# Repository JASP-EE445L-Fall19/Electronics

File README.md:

# Electronics
Schematics, Boards, and Libraries for Lab 11 project

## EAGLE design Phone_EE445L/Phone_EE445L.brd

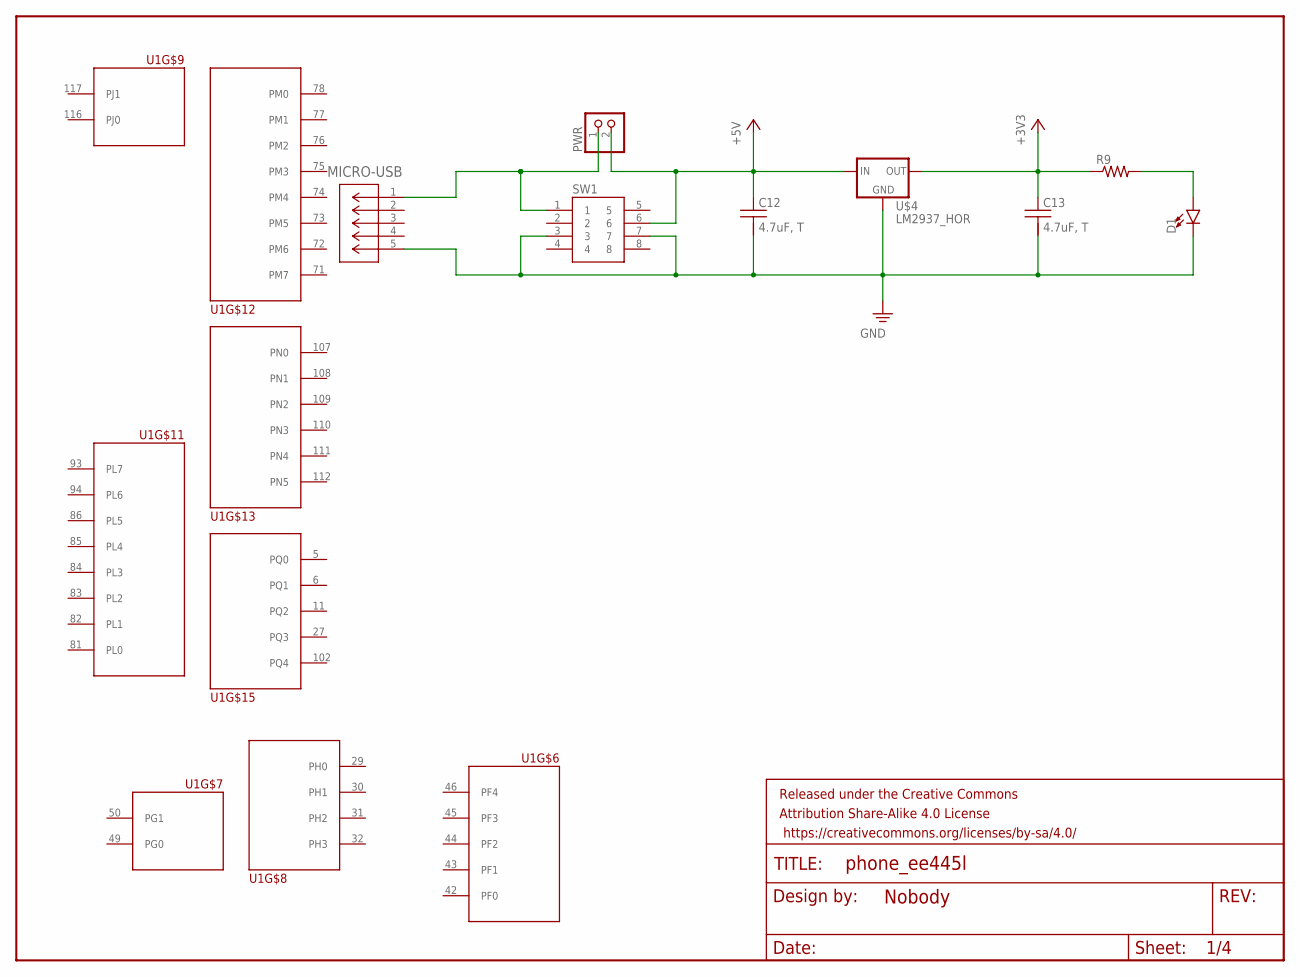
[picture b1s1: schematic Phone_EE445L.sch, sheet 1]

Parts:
C12, C13: 4.7uF, T; CAP200MIL
D1: LED0603; LED-0603
FRAME1: FRAME-LETTERNO_PACKAGE; DUMMY
MICRO-USB: ZX62D-B-5PA8(30); CONN5_ZX62D-B-5PA8
PWR: PINHD-1X2; 1X02
R9: R-US_R0805; R0805
SW1: PUSHBUTTON; PWRBUTTON
U1: TM4C129-MOD; TQFP-128
U$4: LM2937_HOR; TO220

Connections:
5VIN: MICRO-USB.1, PWR.1, SW1.1
+3V3: C13.1, R9.1, U$4.3 (OUT); also elsewhere on the board
+5V: C12.1, PWR.2, SW1.6, U$4.1 (IN); also elsewhere on the board
GND: C12.2, C13.2, D1.C, MICRO-USB.5, SW1.3, SW1.7, U$4.2 (GND); also elsewhere on the board
unnamed: D1.A, R9.2

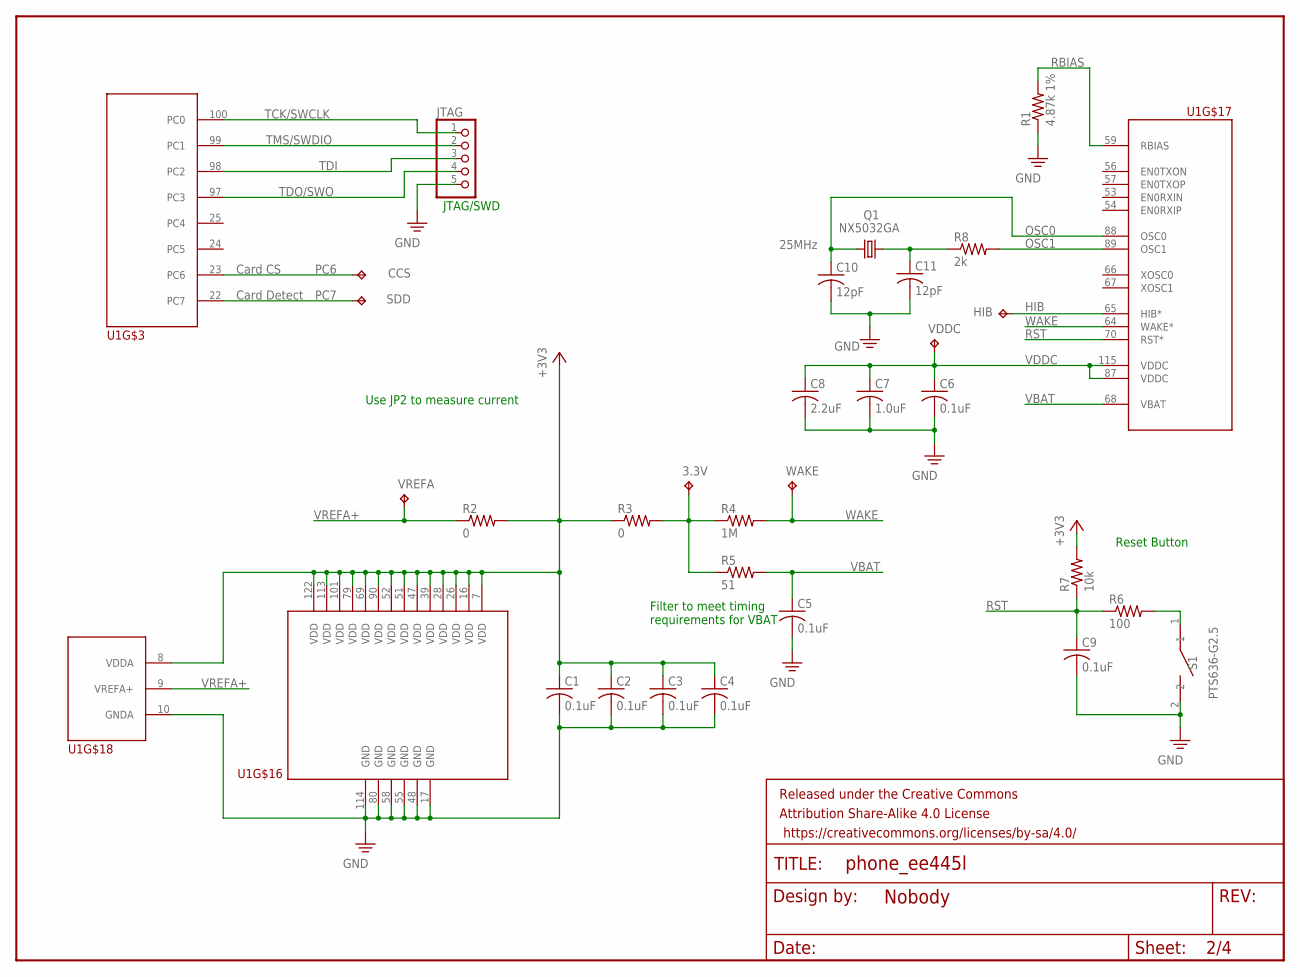
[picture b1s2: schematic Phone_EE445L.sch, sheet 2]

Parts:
3.3V: TP_KEYSTONE500X; P1.1MM
C1, C2, C3, C4, C5, C6, C9: 0.1uF; C0805
C7: 1.0uF; C0805
C8: 2.2uF; C0805
C10, C11: 12pF; C0805
CCS: TP_KEYSTONE500X; P1.1MM
FRAME2: FRAME-LETTERNO_PACKAGE; DUMMY
HIB: TP_KEYSTONE500X; P1.1MM
JTAG: PINHD-1X5; 1X05
Q1: NX5032GA
R1: 4.87k 1%; R0805
R2, R3: 0; R0805
R4: 1M; R0805
R5: 51; R0805
R6: 100; R0805
R7: 10k; R0805
R8: 2k; R0805
S1: PTS636-G2.5; PTS636-G
SDD: TP_KEYSTONE500X; P1.1MM
U1: TM4C129-MOD; TQFP-128
VDDC: TP_KEYSTONE500X; P1.1MM
VREFA: TP_KEYSTONE500X; P1.1MM
WAKE: TP_KEYSTONE500X; P1.1MM

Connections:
+3V3: C1.1, C2.1, C3.1, C4.1, R2.2, R3.1, R7.2, U1.7 (VDD), U1.8 (VDDA), U1.16 (VDD), U1.26 (VDD), U1.28 (VDD), U1.39 (VDD), U1.47 (VDD), U1.51 (VDD), U1.52 (VDD), U1.69 (VDD), U1.79 (VDD), U1.90 (VDD), U1.101 (VDD), U1.113 (VDD), U1.122 (VDD); also elsewhere on the board
GND: C1.2, C2.2, C3.2, C4.2, C5.2, C6.2, C7.2, C8.2, C9.2, C10.2, C11.2, JTAG.5, R1.1, S1.2, U1.10 (GNDA), U1.17 (GND), U1.48 (GND), U1.55 (GND), U1.58 (GND), U1.80 (GND), U1.114 (GND); also elsewhere on the board
HIB: HIB.TP, U1.65 (HIB*)
unnamed: C11.1, Q1.1, R8.1
unnamed: R6.2, S1.1
OSC0: C10.1, Q1.2, U1.88 (OSC0)
OSC1: R8.2, U1.89 (OSC1)
PC6: CCS.TP, U1.23 (PC6); also elsewhere on the board
PC7: SDD.TP, U1.22 (PC7); also elsewhere on the board
RBIAS: R1.2, U1.59 (RBIAS)
RST: C9.1, R6.1, R7.1, U1.70 (RST*)
TCK/SWCLK: JTAG.1, U1.100 (PC0)
TDI: JTAG.3, U1.98 (PC2)
TDO/SWO: JTAG.4, U1.97 (PC3)
TMS/SWDIO: JTAG.2, U1.99 (PC1)
VBAT: C5.1, R5.2, U1.68 (VBAT)
VDDC: C6.1, C7.1, C8.1, U1.87 (VDDC), U1.115 (VDDC), VDDC.TP
VREFA+: R2.1, U1.9 (VREFA+), VREFA.TP
WAKE: R4.2, U1.64 (WAKE*), WAKE.TP
WAKEVDD: 3.3V.TP, R3.2, R4.1, R5.1

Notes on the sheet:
JTAG/SWD
Filter to meet timing requirements for VBAT
Use JP2 to measure current
Reset Button
Card CS
Card Detect
25MHz

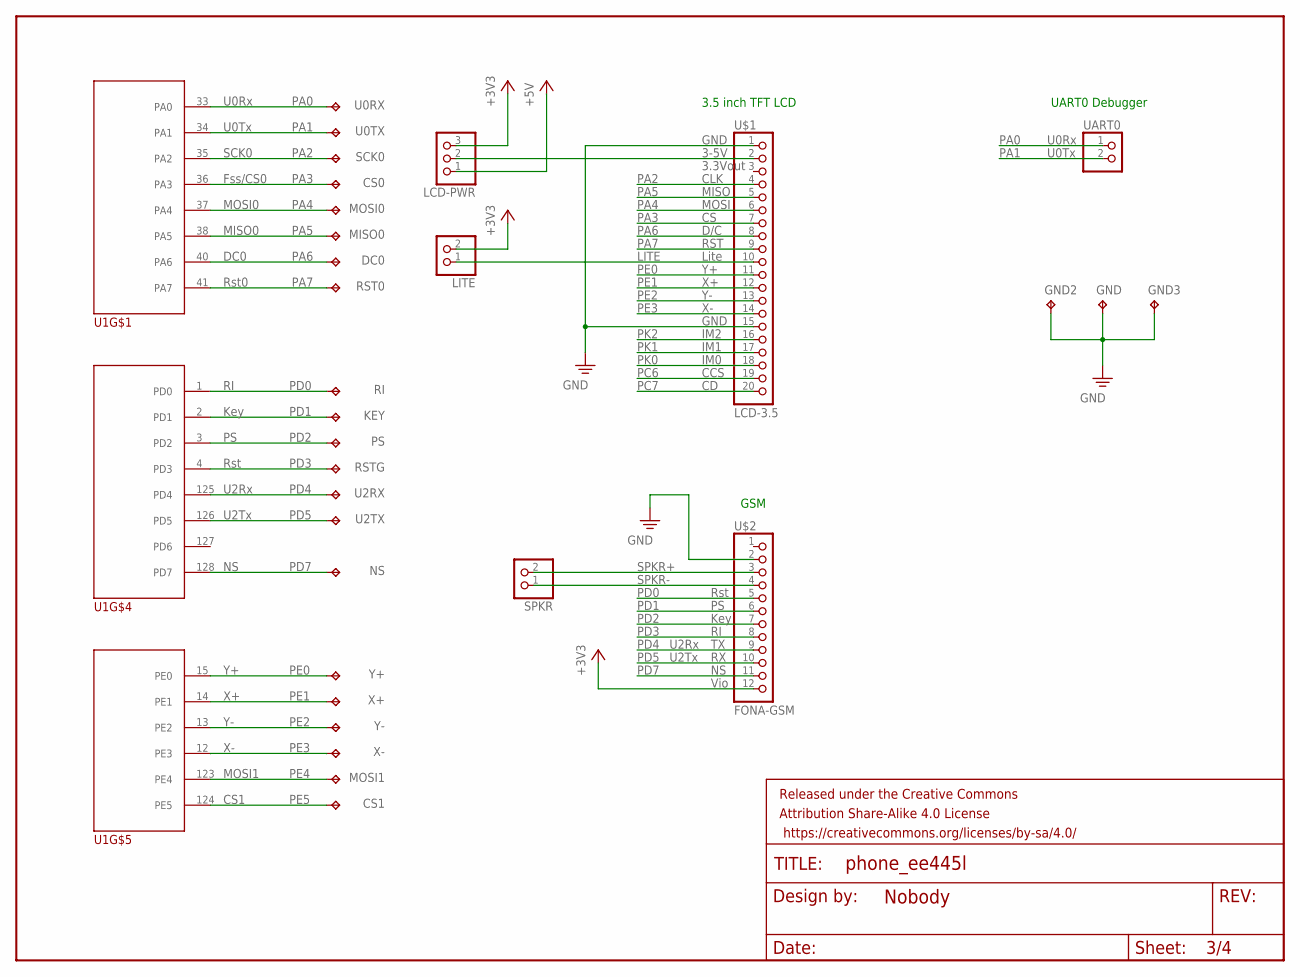
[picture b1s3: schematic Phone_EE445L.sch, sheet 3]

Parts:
CS0, CS1: TP_KEYSTONE500X; P1.1MM
DC0: TP_KEYSTONE500X; P1.1MM
FRAME3: FRAME-LETTERNO_PACKAGE; DUMMY
GND, GND2, GND3: TP_KEYSTONE500X; P1.1MM
KEY: TP_KEYSTONE500X; P1.1MM
LCD-PWR: PINHD-1X3; 1X03
LITE: PINHD-1X2; 1X02
MISO0: TP_KEYSTONE500X; P1.1MM
MOSI0, MOSI1: TP_KEYSTONE500X; P1.1MM
NS: TP_KEYSTONE500X; P1.1MM
PS: TP_KEYSTONE500X; P1.1MM
RI: TP_KEYSTONE500X; P1.1MM
RST0: TP_KEYSTONE500X; P1.1MM
RSTG: TP_KEYSTONE500X; P1.1MM
SCK0: TP_KEYSTONE500X; P1.1MM
SPKR: PINHD-1X2; 1X02
U0RX, U0TX, U2RX, U2TX: TP_KEYSTONE500X; P1.1MM
U1: TM4C129-MOD; TQFP-128
U$1: LCD-3.5; LCD3.5IN
U$2: FONA-GSM; FONA
UART0: PINHD-1X2; 1X02
X+: TP_KEYSTONE500X; P1.1MM
X-: TP_KEYSTONE500X; P1.1MM
Y+: TP_KEYSTONE500X; P1.1MM
Y-: TP_KEYSTONE500X; P1.1MM

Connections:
+3V3: LCD-PWR.3, LITE.2, U$2.12; also elsewhere on the board
+5V: LCD-PWR.1; also elsewhere on the board
GND: GND.TP, GND2.TP, GND3.TP, U$1.1, U$1.15, U$2.2; also elsewhere on the board
LCDPWR: LCD-PWR.2, U$1.2
LITE: LITE.1, U$1.10
PA0: U0RX.TP, U1.33 (PA0), UART0.1
PA1: U0TX.TP, U1.34 (PA1), UART0.2
PA2: SCK0.TP, U1.35 (PA2), U$1.4
PA3: CS0.TP, U1.36 (PA3), U$1.7
PA4: MOSI0.TP, U1.37 (PA4), U$1.6
PA5: MISO0.TP, U1.38 (PA5), U$1.5
PA6: DC0.TP, U1.40 (PA6), U$1.8
PA7: RST0.TP, U1.41 (PA7), U$1.9
PC6: U$1.19; also elsewhere on the board
PC7: U$1.20; also elsewhere on the board
PD0: RI.TP, U1.1 (PD0), U$2.5
PD1: KEY.TP, U1.2 (PD1), U$2.6
PD2: PS.TP, U1.3 (PD2), U$2.7
PD3: RSTG.TP, U1.4 (PD3), U$2.8
PD4: U1.125 (PD4), U2RX.TP, U$2.9
PD5: U1.126 (PD5), U2TX.TP, U$2.10
PD7: NS.TP, U1.128 (PD7), U$2.11
PE0: U1.15 (PE0), U$1.11, Y+.TP
PE1: U1.14 (PE1), U$1.12, X+.TP
PE2: U1.13 (PE2), U$1.13, Y-.TP
PE3: U1.12 (PE3), U$1.14, X-.TP
PE4: MOSI1.TP, U1.123 (PE4); also elsewhere on the board
PE5: CS1.TP, U1.124 (PE5); also elsewhere on the board
PK0: U$1.18
PK1: U$1.17
PK2: U$1.16
SPKR+: SPKR.2, U$2.3
SPKR-: SPKR.1, U$2.4

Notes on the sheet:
3.5 inch TFT LCD
GSM
Vio
Key
Rst
U2Rx
U2Tx
GND
3-5V
3.3Vout
CLK
MISO
MOSI
D/C
RST
Lite
IM2
IM1
IM0
CCS
U0Rx
U0Tx
SCK0
Fss/CS0
MOSI0
MISO0
DC0
Rst0
UART0 Debugger
CS1
MOSI1

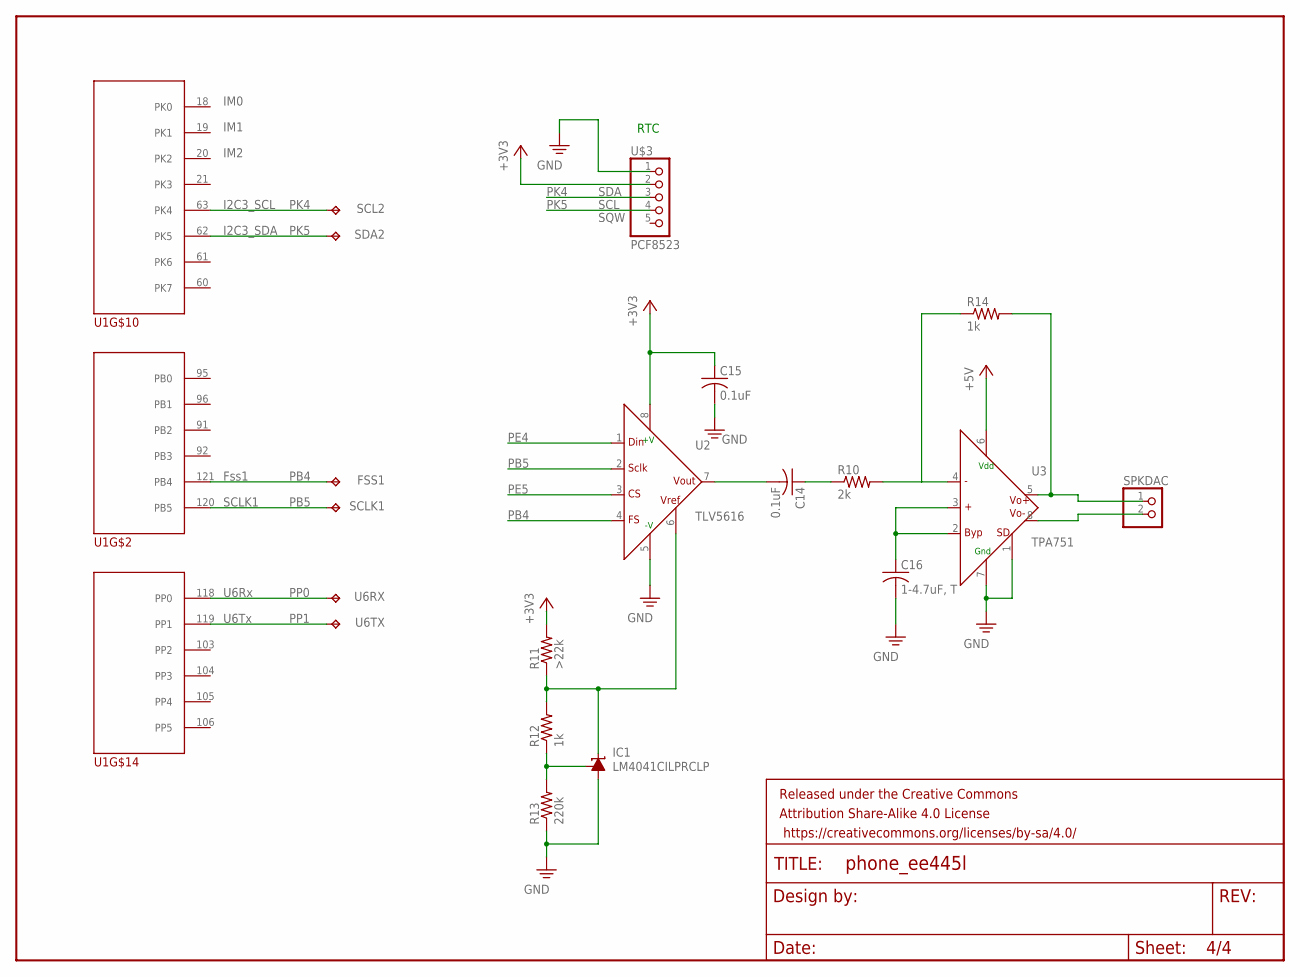
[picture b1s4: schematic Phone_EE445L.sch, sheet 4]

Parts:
C14, C15: 0.1uF; C0805
C16: 1-4.7uF, T; C0805
FRAME4: FRAME-LETTERNO_PACKAGE; DUMMY
FSS1: TP_KEYSTONE500X; P1.1MM
IC1: LM4041CILPRCLP; LP_O-PBCY-W3
R10: 2k; R0805
R11: >22k; R0805
R12, R14: 1k; R0805
R13: 220k; R0805
SCL2: TP_KEYSTONE500X; P1.1MM
SCLK1: TP_KEYSTONE500X; P1.1MM
SDA2: TP_KEYSTONE500X; P1.1MM
SPKDAC: PINHD-1X2; 1X02
U1: TM4C129-MOD; TQFP-128
U2: TLV5616; DIL08
U3: TPA751; SO08
U6RX, U6TX: TP_KEYSTONE500X; P1.1MM
U$3: PCF8523

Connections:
+3V3: C15.1, R11.2, U2.8 (VDD), U$3.2; also elsewhere on the board
+5V: U3.6 (VDD); also elsewhere on the board
AMPIN: R10.2, R14.1, U3.4 (IN-)
DACOUT: C14.2, U2.7 (OUT)
GND: C15.2, C16.2, IC1.3 (A), R13.1, U2.5 (AGND), U3.1 (SHUTDOWN), U3.7 (GND), U$3.1; also elsewhere on the board
HPF: C14.1, R10.1
unnamed: R14.2, SPKDAC.1, U3.5 (VO+)
unnamed: SPKDAC.2, U3.8 (VO-)
unnamed: C16.1, U3.2 (BYPASS), U3.3 (IN+)
PB4: FSS1.TP, U1.121 (PB4), U2.4 (FS)
PB5: SCLK1.TP, U1.120 (PB5), U2.2 (SCLK)
PE4: U2.1 (DIN); also elsewhere on the board
PE5: U2.3 (CS); also elsewhere on the board
PK4: SCL2.TP, U1.63 (PK4), U$3.3
PK5: SDA2.TP, U1.62 (PK5), U$3.4
PP0: U1.118 (PP0), U6RX.TP
PP1: U1.119 (PP1), U6TX.TP
SHUNT: IC1.1 (FB), R12.1, R13.2
VREF: IC1.2 (C), R11.1, R12.2, U2.6 (REFIN)

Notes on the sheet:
I2C3_SCL
I2C3_SDA
RTC
SDA
SCL
SQW
IM2
IM1
IM0
Fss1
SCLK1
U6Rx
U6Tx

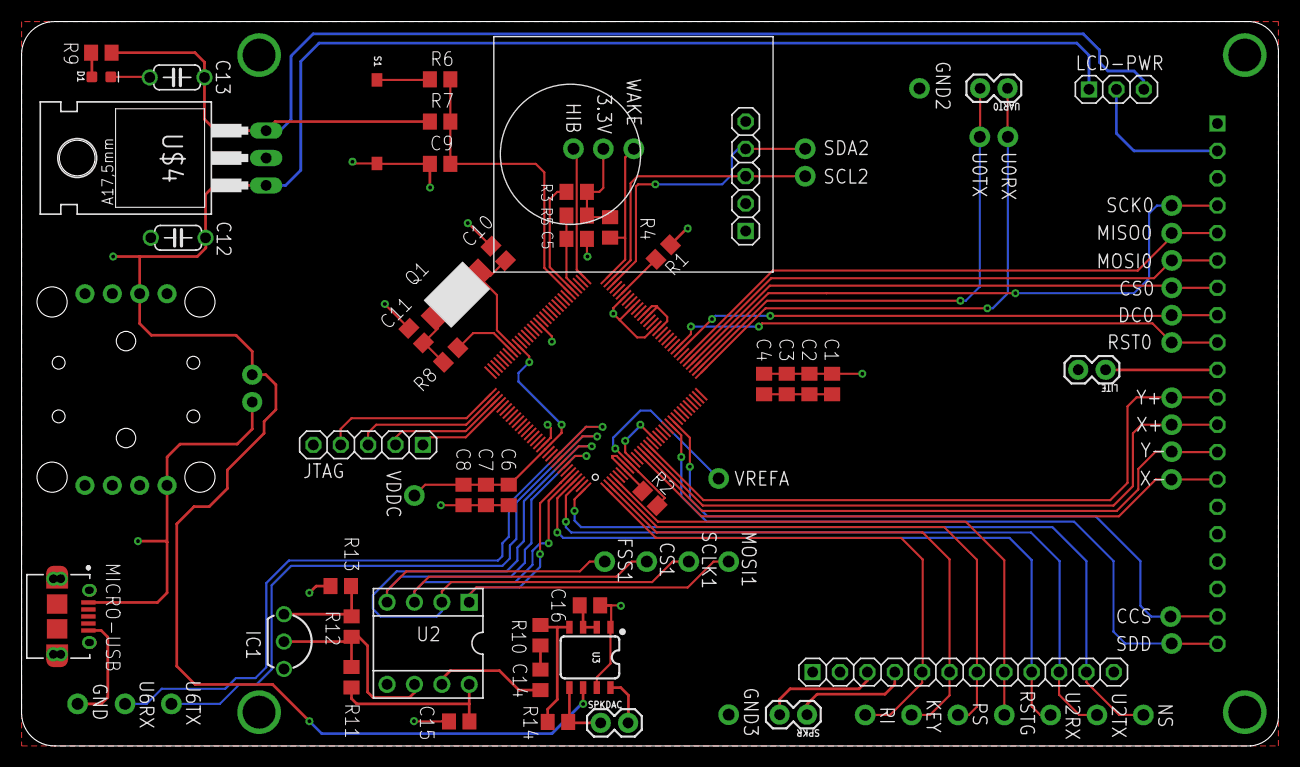
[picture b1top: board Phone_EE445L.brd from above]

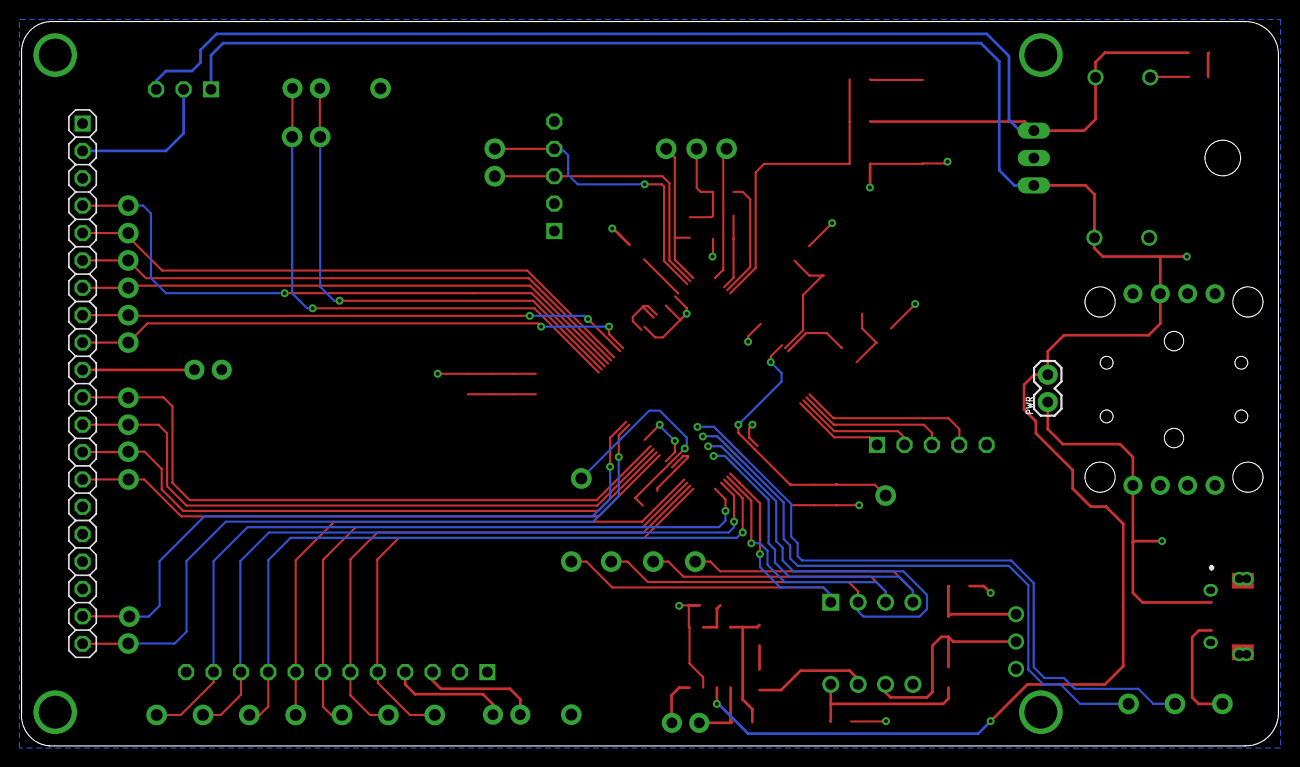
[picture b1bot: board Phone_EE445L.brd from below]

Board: 2 copper layers, 116.6 x 67.2 mm, 91 parts (3 on the bottom side), 62 nets.

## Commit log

2019-10-22 Libraries for EAGLE
2019-10-23 Starting SCH and BRD for TM4C129
2019-10-24 Worked on SCH using PCBArtist and TM4C1234
2019-10-24 Updated SCH and placed into lab 7 starter SCH/BRD
2019-10-24 Completed schematic for PCB Artist lab 7
2019-10-24 Organized PCB Artist schematic for lab 7
2019-10-28 Started several versions.
2019-10-28 Finished tracing
2019-10-28 Fixed disconnected ground planes
2019-10-31 Completed Minimum Board in PCB Artist
2019-10-31 Added Ground Plane on PCB Artist Version
2019-11-09 Continued finishing final board
2019-11-09 Updated SCH pdf
2019-11-10 Finished Final Board on EAGLE
2019-11-10 Updated all libraries

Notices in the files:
parts and their libraries:
SparkFun-Aesthetics: Licensing: Creative Commons ShareAlike 4.0 International - https://creativecommons.org/licenses/by-sa/4.0
SparkFun-Aesthetics: Released under the Creative Commons Attribution Share-Alike 4.0 License
SparkFun-Aesthetics: https://creativecommons.org/licenses/by-sa/4.0
